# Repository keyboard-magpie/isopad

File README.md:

# isopad
PCB files and case STL for a pro-micro compatible ISO enter single key macropad

Build guide: https://imgur.com/a/puC9ops

For the adventurous: the switch is connected to pro micro pin F4.

**FAQ:**

Can it do RGB? Not easily. You can wire RGB strips to the spare pro micro pins, perhaps.

Can I turn the LED off? Yes, unplug the isopad :D

Is it in main QMK? No, at present just the precompiled VIA hex is offered.

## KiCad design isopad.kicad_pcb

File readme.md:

https://imgur.com/a/puC9ops

Recursive or wot, ey?

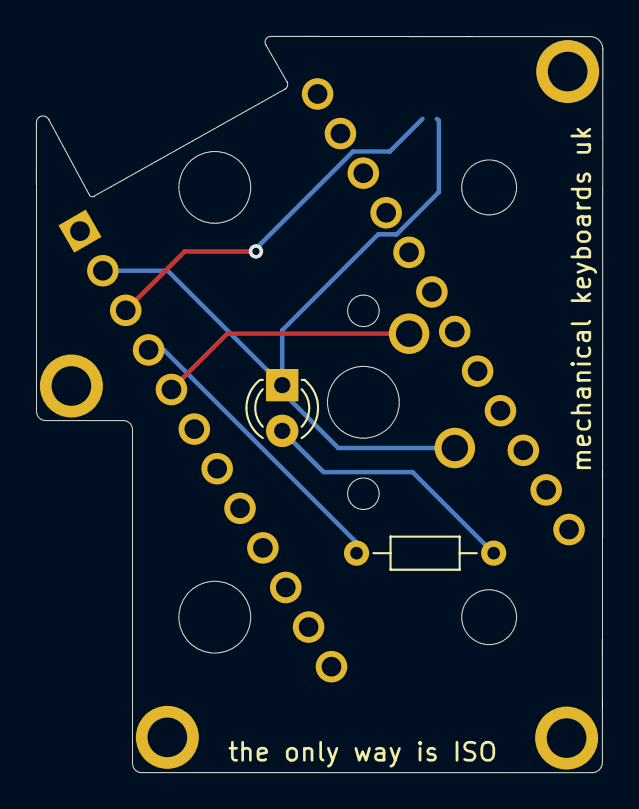
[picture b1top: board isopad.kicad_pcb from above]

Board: 2 copper layers, 31.5 x 40.9 mm, 9 parts (0 on the bottom side), 5 nets.

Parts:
 : LED; LED_D3.0mm_FlatTop
H1, H2, H3, H4: MountingHole; Generic-Mounthole
K?1: KEYSW; MXOnly-ISO-ROTATED-ReversedStabilizers-NoLED
R1: R; R_Axial_DIN0204_L3.6mm_D1.6mm_P7.62mm_Horizontal
SW1: SW_PUSH; SOLDER_JUMPER_2
U1: Pro_Micro

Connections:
unnamed: .1, K?1.2, SW1.2, U1.2
unnamed: .2, R1.2
unnamed: K?1.1, U1.5
unnamed: R1.1, U1.4
unnamed: SW1.1, U1.3

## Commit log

2021-04-07 Rename isopad_via.hex to AA_isopad_via.hex
2021-04-07 Rename fp-info-cache to kicad/fp-info-cache
2021-04-07 Rename fp-lib-table to kicad/fp-lib-table
2021-04-07 Rename isopad-Edge_Cuts.dxf to case/isopad-Edge_Cuts.dxf
2021-04-07 Rename isopad-Edge_Cuts.svg to case/isopad-Edge_Cuts.svg
2021-04-07 Rename isopad-cache.lib to kicad/isopad-cache.lib
2021-04-07 Rename isopad-F_Mask.dxf to case/isopad-F_Mask.dxf
2021-04-07 Rename isopad.kicad_pcb to kicad/isopad.kicad_pcb
2021-04-07 Rename isopad.kicad_pcb-bak to kicad/isopad.kicad_pcb-bak
2021-04-07 Rename isopad.pro to kicad/isopad.pro
2021-04-07 Rename isopad.sch to kicad/isopad.sch
2021-04-07 Rename isopad.step to case/isopad.step
2021-04-07 Rename isopad.sch-bak to kicad/isopad.sch-bak
2021-04-07 Rename sym-lib-table to kicad/sym-lib-table
2021-04-07 tidyup
2021-04-07 rename files
